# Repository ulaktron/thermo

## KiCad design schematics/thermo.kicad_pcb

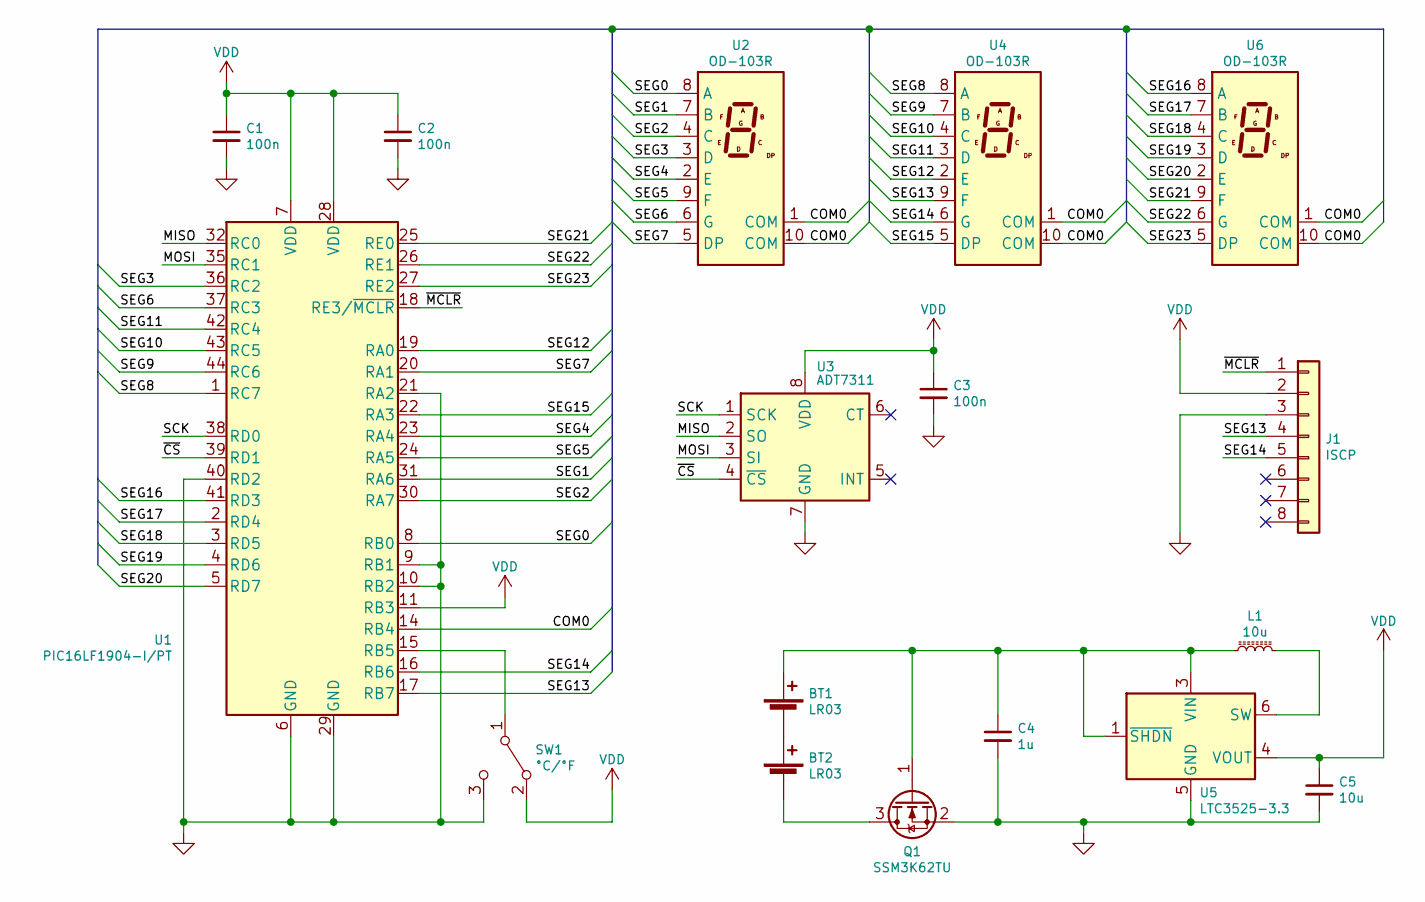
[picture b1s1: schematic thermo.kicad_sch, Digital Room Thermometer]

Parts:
BT1, BT2: LR03; 1020; Part 1020
C1, C2, C3: 100n; C_0603_1608Metric; Part CL10B104KC8NNNC
C4: 1u; C_0805_2012Metric; Part CL21B105KBFNNNE
C5: 10u; C_1210_3225Metric; Part CGA6P1X7R1E106K250AC
J1: ISCP; PinHeader_1x08_P2.54mm_Vertical
L1: 10u; L_Taiyo-Yuden_NR-30xx; Part NRH3012T100MN
Q1: SSM3K62TU; UFM; Part SSM3K62TU,LF
SW1: °C/°F; MSS-102545-14A-V-SMT; Part MSS-102545-14A-V-SMT
U1: PIC16LF1904-I/PT; TQFP-44_10x10mm_P0.8mm; Part PIC16LF1904-I/PT
U2, U4, U6: OD-103R; Part OD-103R
U3: ADT7311; SOIC-8_3.9x4.9mm_P1.27mm; Part ADT7311WTRZ-RL7
U5: LTC3525-3.3; SOT-363_SC-70-6; Part LTC3525ESC6-3.3#TRMPBF

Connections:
/COM0: U1.14 (RB4), U2.1 (COM), U2.10 (COM), U4.1 (COM), U4.10 (COM), U6.1 (COM), U6.10 (COM)
/MISO: U1.32 (RC0), U3.2 (SO)
/MOSI: U1.35 (RC1), U3.3 (SI)
/SCK: U1.38 (RD0), U3.1 (SCK)
/SEG0: U1.8 (RB0), U2.8 (A)
/SEG1: U1.31 (RA6), U2.7 (B)
/SEG2: U1.30 (RA7), U2.4 (C)
/SEG3: U1.36 (RC2), U2.3 (D)
/SEG4: U1.23 (RA4), U2.2 (E)
/SEG5: U1.24 (RA5), U2.9 (F)
/SEG6: U1.37 (RC3), U2.6 (G)
/SEG7: U1.20 (RA1), U2.5 (DP)
/SEG8: U1.1 (RC7), U4.8 (A)
/SEG9: U1.44 (RC6), U4.7 (B)
/SEG10: U1.43 (RC5), U4.4 (C)
/SEG11: U1.42 (RC4), U4.3 (D)
/SEG12: U1.19 (RA0), U4.2 (E)
/SEG13: J1.4, U1.17 (RB7), U4.9 (F)
/SEG14: J1.5, U1.16 (RB6), U4.6 (G)
/SEG15: U1.22 (RA3), U4.5 (DP)
/SEG16: U1.41 (RD3), U6.8 (A)
/SEG17: U1.2 (RD4), U6.7 (B)
/SEG18: U1.3 (RD5), U6.4 (C)
/SEG19: U1.4 (RD6), U6.3 (D)
/SEG20: U1.5 (RD7), U6.2 (E)
/SEG21: U1.25 (RE0), U6.9 (F)
/SEG22: U1.26 (RE1), U6.6 (G)
/SEG23: U1.27 (RE2), U6.5 (DP)
/~CS: U1.39 (RD1), U3.4 (~CS)
/~MCLR: J1.1, U1.18 (RE3/~MCLR)
GND: C1.2, C2.2, C3.2, C4.2, C5.2, J1.3, Q1.2 (S), SW1.3 (B), U1.6 (GND), U1.9 (RB1), U1.10 (RB2), U1.21 (RA2), U1.29 (GND), U1.40 (RD2), U3.7 (GND), U5.2 (GND), U5.5 (GND)
unnamed: BT1.1 (+), C4.1, L1.1, Q1.1 (G), U5.1 (~SHDN), U5.3 (VIN)
unnamed: BT1.2 (-), BT2.1 (+)
unnamed: BT2.2 (-), Q1.3 (D)
unnamed: L1.2, U5.6 (SW)
unnamed: SW1.1 (C), U1.15 (RB5)
VDD: C1.1, C2.1, C3.1, C5.1, J1.2, SW1.2 (A), U1.7 (VDD), U1.11 (RB3), U1.28 (VDD), U3.8 (VDD), U5.4 (VOUT)

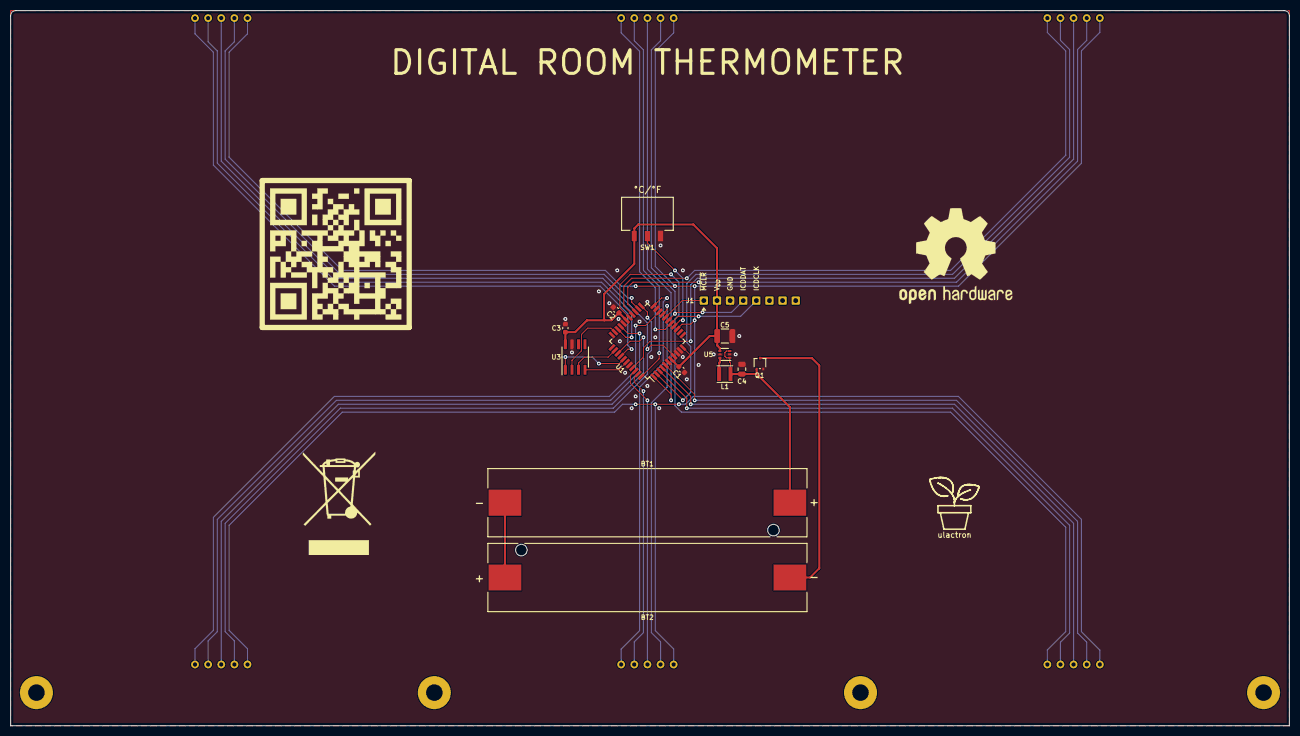
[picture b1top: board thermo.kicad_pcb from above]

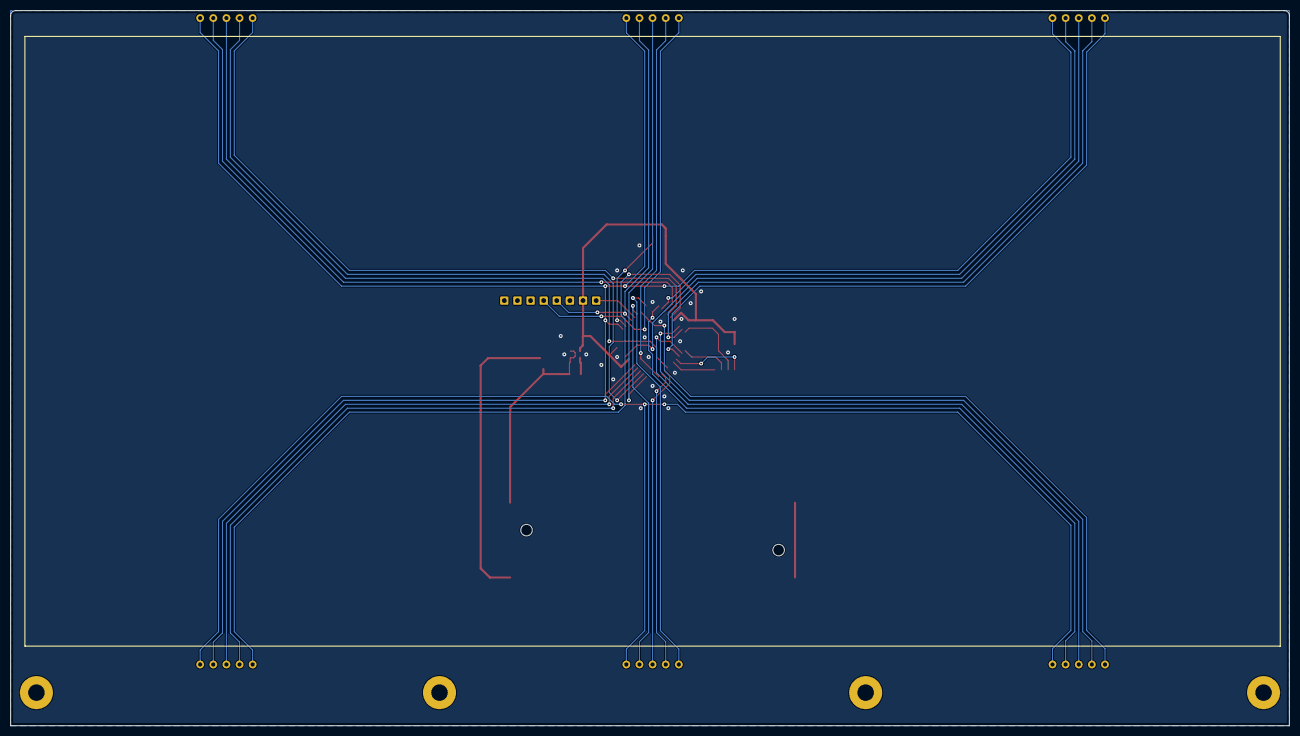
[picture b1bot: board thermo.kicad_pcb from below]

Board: 2 copper layers, 247.5 x 138.4 mm, 17 parts (3 on the bottom side), 37 nets.

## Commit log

2022-07-01 Revision 01

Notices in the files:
schematics/thermo.kicad_pcb:
© 2022 ulaktron
